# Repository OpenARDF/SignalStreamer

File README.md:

# SignalStreamer
A simple, compact, effective 80m radio orienteering transmit antenna

SignalStreamer is an 80-meter-band radio-orienteering (ARDF) transmit antenna kit designed to operate in the Amateur Radio Service 3.5 MHz to 3.7 MHz frequency range. The antenna is the perfect complement to the SignalSlinger 80m transmitter. It even fits into an identical box!

The SignalStreamer project is 100% Open Source. All the KiCad hardware design documents are available for download from this GitHub repository.

User Manual: <a href="https://docs.google.com/document/d/1ixdft7eyVAQ5lvPSUMsNJx15NzzCWhzimSsPBIRxByI/edit?usp=sharing">Assembly & User Manual</a>.

A matching transmitter: <a href="https://github.com/OpenARDF/SignalSlinger">SignalSlinger</a>.

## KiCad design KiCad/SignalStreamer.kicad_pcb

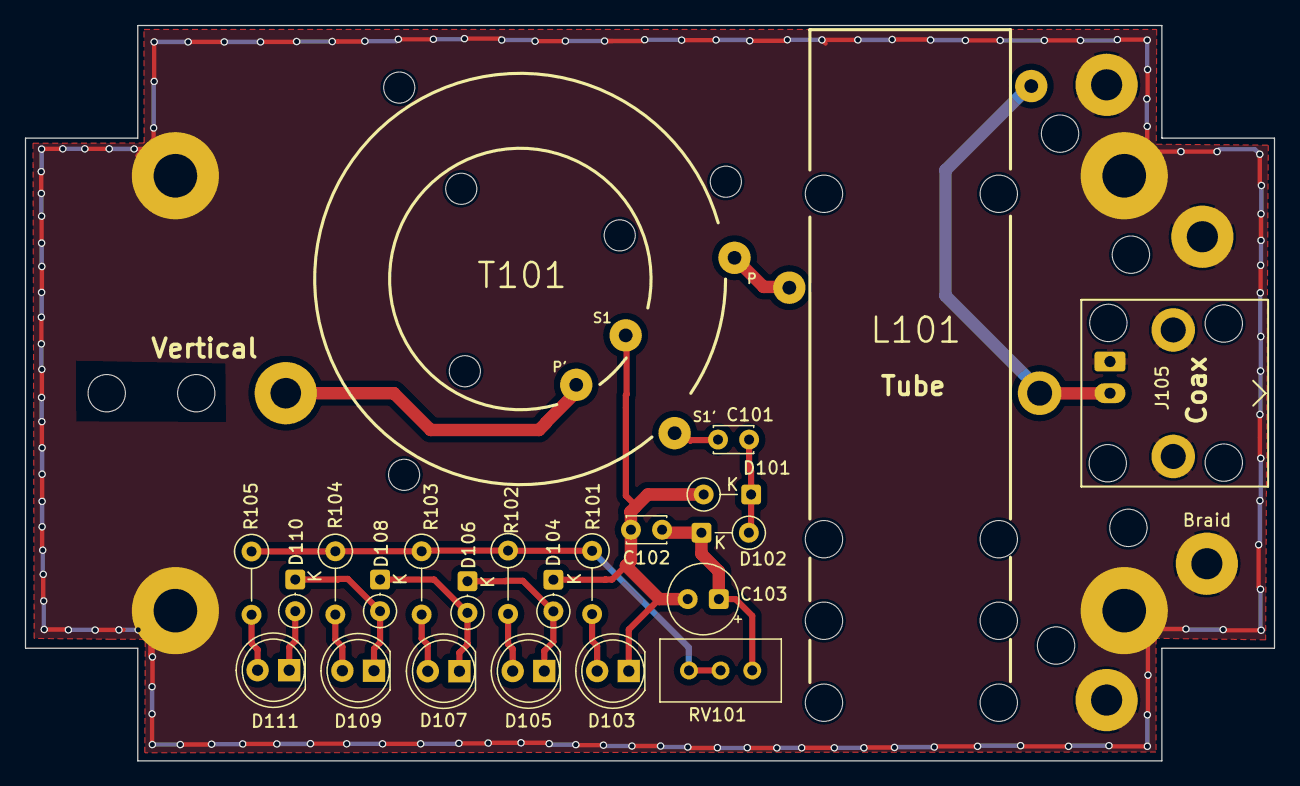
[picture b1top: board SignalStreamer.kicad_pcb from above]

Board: 2 copper layers, 100.3 x 59.1 mm, 23 parts (0 on the bottom side), 16 nets.

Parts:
C101, C102: 470nF; C_Disc_D3.0mm_W2.0mm_P2.50mm
C103: 10uF; CP_Radial_Tantal_D5.5mm_P2.50mm
D101, D102: 1N5711; D_DO-35_SOD27_P3.81mm_Vertical_KathodeUp
D103, D105, D107, D109, D111: WP7113ID; LED_D5.0mm
D104, D106, D108, D110: 1N4148; D_DO-35_SOD27_P2.54mm_Vertical_KathodeUp
J105: Conn_01x02; BNC_Amphenol_B6252HB-NPP3G-50_Horizontal
L101: FB-31-4852; L_Lipstick_Tube_Variable
R101, R102, R103, R104, R105: 470; R_Axial_DIN0207_L6.3mm_D2.5mm_P5.08mm_Vertical
RV101: 2k; Potentiometer_Bourns_3296W_Vertical
T101: Coupled_Inductors_2; Core_T130_2_windings_Horiz_TH

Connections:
unnamed: C102.2, C103.2, D101.2 (A), D103.1 (K), D104.1 (K), T101.1 (PM)
unnamed: C101.1, D101.1 (K), D102.2 (A)
unnamed: C102.1, C103.1, D102.1 (K), RV101.1
unnamed: D103.2 (A), R101.2
unnamed: D104.2 (A), D105.1 (K), D106.1 (K)
unnamed: D105.2 (A), R102.2
unnamed: D106.2 (A), D107.1 (K), D108.1 (K)
unnamed: D107.2 (A), R103.2
unnamed: D108.2 (A), D109.1 (K), D110.1 (K)
unnamed: D109.2 (A), R104.2
unnamed: D110.2 (A), D111.1 (K)
unnamed: D111.2 (A), R105.2
unnamed: J105.1, L101.2
unnamed: R101.1, R102.1, R103.1, R104.1, R105.1, RV101.2, RV101.3
unnamed: C101.2, T101.2 (IN+)
unnamed: L101.1, T101.4 (OUT1B)

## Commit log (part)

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2026-01-01 Create Schematic.pdf
    Added schematic PDF
2026-01-03 Enhance README with detailed SignalStreamer description
    Expanded the description of the SignalStreamer antenna kit, including its compatibility with the SignalSlinger transmitter and open-source status.
2026-01-03 Add user manual note and link to SignalSlinger
    Updated README to include user manual information and link to SignalSlinger.
2026-01-03 Dev
    Schematic and board updates
2026-01-03 Ver X1.0
    Copied latest changes from backup project
2026-01-04 Development
    Updates
2026-01-04 Add image to README for SignalStreamer
    Added an image to the README for better visualization.
2026-01-04 Fix hyphenation in SignalStreamer description
    Corrected hyphenation in the description of SignalStreamer.
2026-01-04 Correct image link for SignalStreamer PCB
    Fixed image link formatting in README.md
2026-01-04 Rename Image
    For Readme
2026-01-04 Fix image path in README.md
2026-01-04 Fix image link formatting in README.md
2026-01-05 Development
    PCB Updates
2026-01-09 Ver 1.0
    Redesign of LED tuning indicator. All gerbers updated.
2026-01-10 PCB Updates
    Corrects a problem with horizontal radials connection to coax ground
2026-01-10 PCB
    Minor changes to improve clearances
2026-01-11 PCB
    Minor PCB tweaks
    Removes all DRC warnings
2026-01-24 Update user manual link in README
    Updated user manual link and removed placeholder text.
2026-01-26 Cleanup
    .gitignore update
    Removed .DS_Store files
    Removed old .html file
2026-02-02 Beautify Schematic
    Minor edits to schematic diagram component positions. No changes functionally.
